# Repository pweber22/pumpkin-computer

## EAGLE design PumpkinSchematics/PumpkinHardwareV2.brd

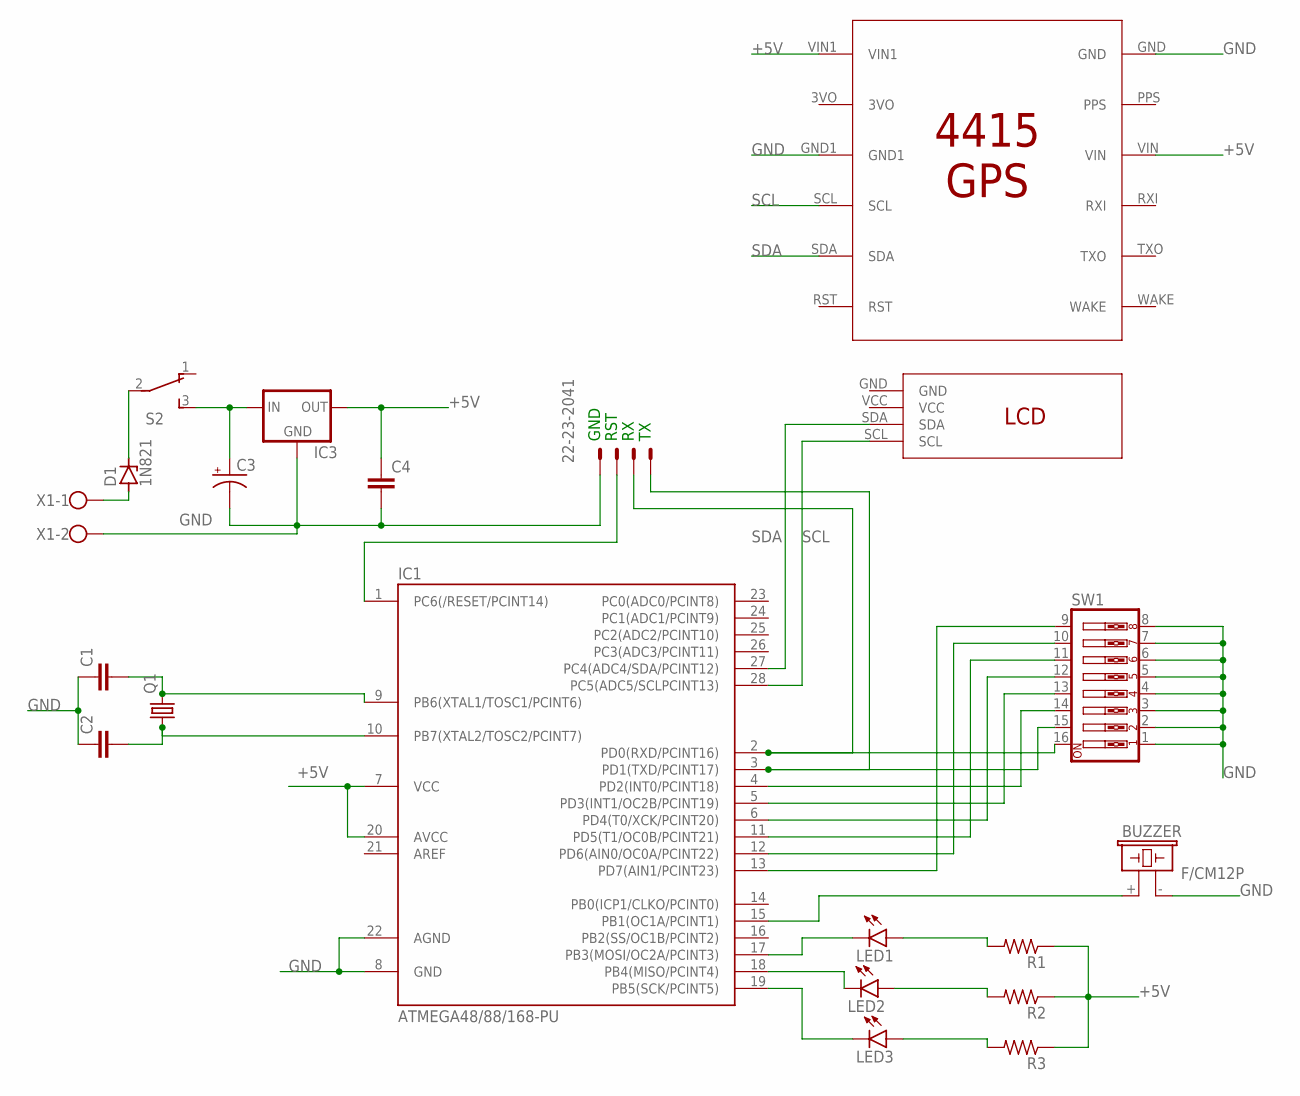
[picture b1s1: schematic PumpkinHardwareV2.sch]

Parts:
BUZZER: F/CM12P
C1, C2, C4: C2.5/2; C2.5-2
C3: CPOL-USE3.5-8; E3,5-8
D1: 1N821; DO35Z10
GPS: 4415
IC1: ATMEGA48/88/168-PU; DIL28-3
IC3: 78XXL
LED1: TLLG4400; LED3MM
LED2: TLLY4400; LED3MM
LED3: TLLR4400; LED3MM
Q1: CRYSTALHC49S; HC49/S
R1, R2, R3: R-US_0207/10; 0207/10
S2: TL36PO; TL3XPO
SW1: SW_DIP-8; EDG-08
U$1: I2C_LCD
X1: W237-102
X2: 22-23-2041

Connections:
+5V: C4.1, GPS.VIN, GPS.VIN1, IC1.7 (VCC), IC1.20 (AVCC), IC3.OUT, R1.1, R2.1, R3.1
GND: BUZZER.- (2), C1.1, C2.1, C3.-, C4.2, GPS.GND, GPS.GND1, IC1.8 (GND), IC1.22 (AGND), IC3.GND, SW1.1, SW1.2, SW1.3, SW1.4, SW1.5, SW1.6, SW1.7, SW1.8, X1.2, X2.1
unnamed: LED1.A, R1.2
unnamed: IC1.18 (PB4(MISO/PCINT4)), LED2.K (C)
unnamed: IC1.19 (PB5(SCK/PCINT5)), LED3.K (C)
unnamed: LED2.A, R2.2
unnamed: LED3.A, R3.2
unnamed: IC1.17 (PB3(MOSI/OC2A/PCINT3)), LED1.K (C)
unnamed: IC1.13 (PD7(AIN1/PCINT23)), SW1.9
unnamed: IC1.12 (PD6(AIN0/OC0A/PCINT22)), SW1.10
unnamed: IC1.11 (PD5(T1/OC0B/PCINT21)), SW1.11
unnamed: IC1.6 (PD4(T0/XCK/PCINT20)), SW1.12
unnamed: IC1.5 (PD3(INT1/OC2B/PCINT19)), SW1.13
unnamed: IC1.4 (PD2(INT0/PCINT18)), SW1.14
unnamed: IC1.3 (PD1(TXD/PCINT17)), SW1.15, X2.4
unnamed: D1.C, S2.2
unnamed: C2.2, IC1.10 (PB7(XTAL2/TOSC2/PCINT7)), Q1.1
unnamed: C1.2, IC1.9 (PB6(XTAL1/TOSC1/PCINT6)), Q1.2
unnamed: D1.A, X1.1
unnamed: C3.+, IC3.IN, S2.3 (S)
unnamed: BUZZER.+ (1), IC1.15 (PB1(OC1A/PCINT1))
unnamed: IC1.1 (PC6(/RESET/PCINT14)), X2.2
unnamed: IC1.2 (PD0(RXD/PCINT16)), SW1.16, X2.3
SCL: GPS.SCL, IC1.28 (PC5(ADC5/SCLPCINT13)), U$1.SCL
SDA: GPS.SDA, IC1.27 (PC4(ADC4/SDA/PCINT12)), U$1.SDA

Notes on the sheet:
GND
RST

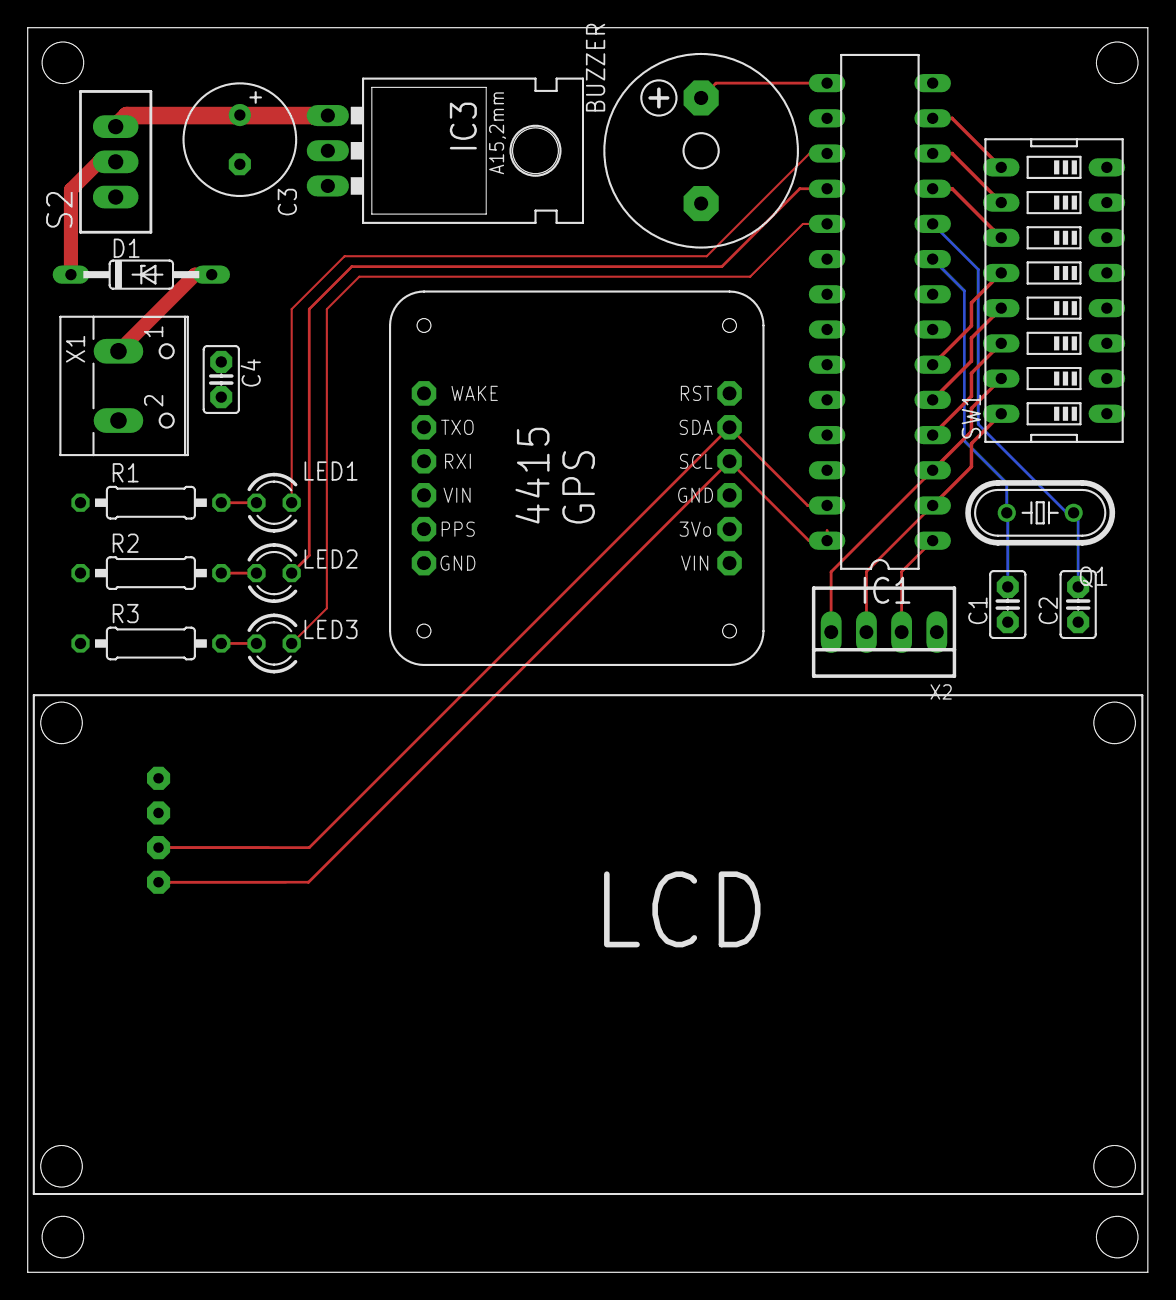
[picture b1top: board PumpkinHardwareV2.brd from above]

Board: 2 copper layers, 80.8 x 89.8 mm, 21 parts (0 on the bottom side), 25 nets.

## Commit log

2022-01-11 first version of complete flight computer software
2022-01-12 end of day 1 testing
2022-01-13 fixed
2022-01-15 created develop branch
2022-01-15 work done on bus
2022-01-15 removed commented redundant lines
2022-01-15 fixed some issues with coordinates and cleaned up some variables
2022-01-15 optimization
2022-01-15 removed serial print statements
2022-01-21 Begin setting up software for new hardware
2022-01-25 code for new hardware complete
2022-01-27 added hardware schematics
2022-01-29 changed upper byte selection to change wind conditions
2022-02-02 added interrupt for simulation updates
2022-02-03 updates calculations every 2 secs
2022-02-07 fixed interrupt system somewhat, doesn't always start properly
2022-02-08 optimized display updates and update sim based on internal timer
2022-02-08 added gps check to startup and re-implemented interrupt based simulation updates
2022-02-09 changed alt for target 0 for timing tests, added business 30 to targets 3 and 4
2022-02-09 cleaning up files
2022-02-09 Removed extra data from GPS communication, now uses RMCONLY instead of RMCGGA NMEA protocol
2022-02-09 added targeting mode to get target coordinates, activated by most significant bit switch after startup
2022-02-09 Needs better coordinates for targets
2022-02-10 increased precision of flight path calculations
2022-02-12 improved coordinate precision using double instead of float
2022-02-12 fixed merge conflict
2022-02-15 converted float math to long math
2022-03-14 Updated software for Teensy processor and serial interface to computer for display
2022-03-14 progress on serial interface to computer
2022-03-21 more work on interface, added header file for wind data
2022-03-21 fixed path error calculation
2022-03-23 Added v3 schematic
2022-03-30 Added Lightbar
2022-03-30 Added light bar control and targeting state
2022-04-05 Actually fixed error calculation (maybe)
2022-04-05 Organized 3.1 schematic
2022-04-11 still working on error
2022-04-18 removed extra blank space
2022-05-20 minor changes
2022-05-20 testing
2022-05-20 created a new Target header file for privacy
2022-07-06 updated drop sequence
2022-07-09 polishing drop sequence
